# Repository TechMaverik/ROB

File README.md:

# ROB - Robotics On Board
<image src="static/studio.png" height=300px width=300px></image>

The project ROB is a robotic arm developed with in-house software, hardware assembly, and custom PCB design. ROB-Studio is the software used to interact with the robot.  
Version 1.0 features a 5-degree-of-freedom robotic arm powered by 6 servo motors, capable of lifting up to 50 g of payload. ROB-Studio is made using the software framework 
called HL-Engine 3, which acts as a middleware to communicate with Hardware and Software.

## ROB version 1.0
## Components Used
1. Servo Motor MG995
2. Servo Motor SG90
3. PCA9685 Servomotor Driver
4. OLED Display 128 x 64
5. ESP32

## Firmware
The baremetal interfacing and control system code is written in Micropython for ESP32

## Procedure of connection of motors and arm pieces
1. Upload the files under Firmware Folder
2. Make sure to provide a valid SSID and Password in the code as per your network connection.
3. Connect the servo motors from channel 0 to channel 5 in order base,shoulder,elbow,wrist-pitch,wrist-yaw,pick.
4. Make sure the servo is set to 90 degress.
5. Adjust the home position according to your requirements.

## Procedure to run the ROB-Studio
1. Install python 3.10 or later version
2. Create a virtual environment called .robot using the command <code>python3 -m venv .robot</code> ( One time )
3. Now run <code> pip3 install -r requirements.txt </code> ( One time )
4. Now run <code> chmod +x ./launcher </code> ( One time )
5. <b>To run the app run ./launcher.py </b>

## Alternative steps to run ROB-Studio
1. Follow the steps till line number 3
2. Now run <code>source .rob/bin/activate </code>
3. Now run <code>python run.py</code>

## ROB Studio
<image src="static/StudioHome.png"></image>
You can control the robor arm by adjusting the slider of each joints and by pressing the Move button. Inorder to record the particular orienttation, one has to adjust the arm and press the Record Button.
<image src="static/StudioRecord.png"></image>
Your recorded operations can be seen under Record and Play tab. You can start running the application by pressing the Play button.
<image src="static/StudioDevice.png"></image>
You can connect the ROB studion to the ROB by entering the IP Address displayed on ROB OLED Display. A sample is shown above.

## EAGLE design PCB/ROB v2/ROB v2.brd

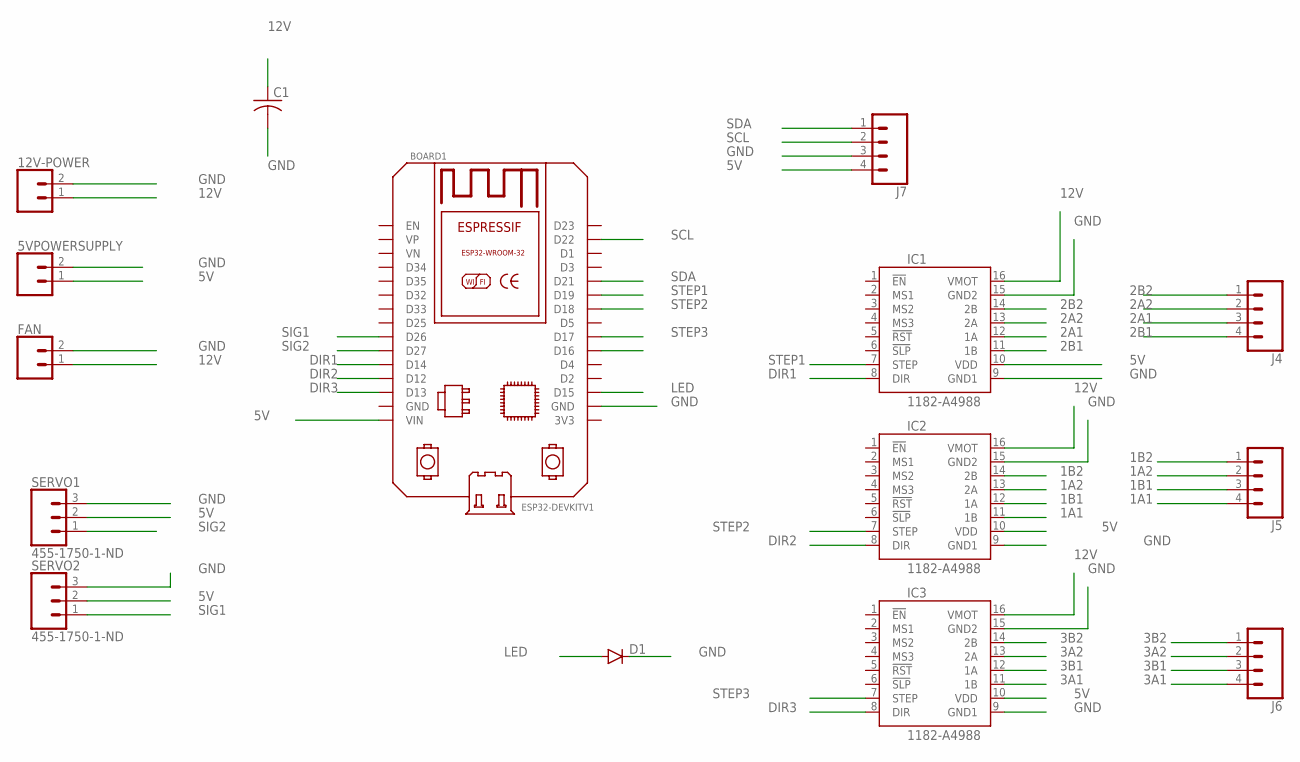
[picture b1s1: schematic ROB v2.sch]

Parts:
5VPOWERSUPPLY, 12V-POWER: CONN_02; 1X02
BOARD1: ESP32DEVKITV1; ESP32-DEVKITV1
C1: C-US050-075X075; C050-075X075
D1: DIODE; DIODE-1N4001-KIT
FAN: CONN_02; 1X02
IC1, IC2, IC3: 1182-A4988; A4988
J4, J5, J6: CONN_04LONGPADS; 1X04_LONGPADS
J7: CONN_04LOCK; 1X04_LOCK
SERVO1, SERVO2: 455-1750-1-ND; 1X03

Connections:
1A1: IC2.11 (1B), J5.4
1A2: IC2.13 (2A), J5.2
1B1: IC2.12 (1A), J5.3
1B2: IC2.14 (2B), J5.1
2A1: IC1.12 (1A), J4.3
2A2: IC1.13 (2A), J4.2
2B1: IC1.11 (1B), J4.4
2B2: IC1.14 (2B), J4.1
3A1: IC3.11 (1B), J6.4
3A2: IC3.13 (2A), J6.2
3B1: IC3.12 (1A), J6.3
3B2: IC3.14 (2B), J6.1
5V: 5VPOWERSUPPLY.1, BOARD1.VIN, IC1.10 (VDD), IC2.10 (VDD), IC3.10 (VDD), J7.4, SERVO1.2, SERVO2.2
12V: 12V-POWER.1, C1.1, FAN.1, IC1.16 (VMOT), IC2.16 (VMOT), IC3.16 (VMOT)
DIR1: BOARD1.D14, IC1.8 (DIR)
DIR2: BOARD1.D12, IC2.8 (DIR)
DIR3: BOARD1.D13, IC3.8 (DIR)
GND: 5VPOWERSUPPLY.2, 12V-POWER.2, BOARD1.GND@1 (GND), C1.2, D1.C, FAN.2, IC1.9 (GND1), IC1.15 (GND2), IC2.9 (GND1), IC2.15 (GND2), IC3.9 (GND1), IC3.15 (GND2), J7.3, SERVO1.3, SERVO2.3
LED: BOARD1.D15, D1.A
SCL: BOARD1.D22, J7.2
SDA: BOARD1.D21, J7.1
SIG1: BOARD1.D26, SERVO2.1
SIG2: BOARD1.D27, SERVO1.1
STEP1: BOARD1.D19, IC1.7 (STEP)
STEP2: BOARD1.D18, IC2.7 (STEP)
STEP3: BOARD1.D17, IC3.7 (STEP)

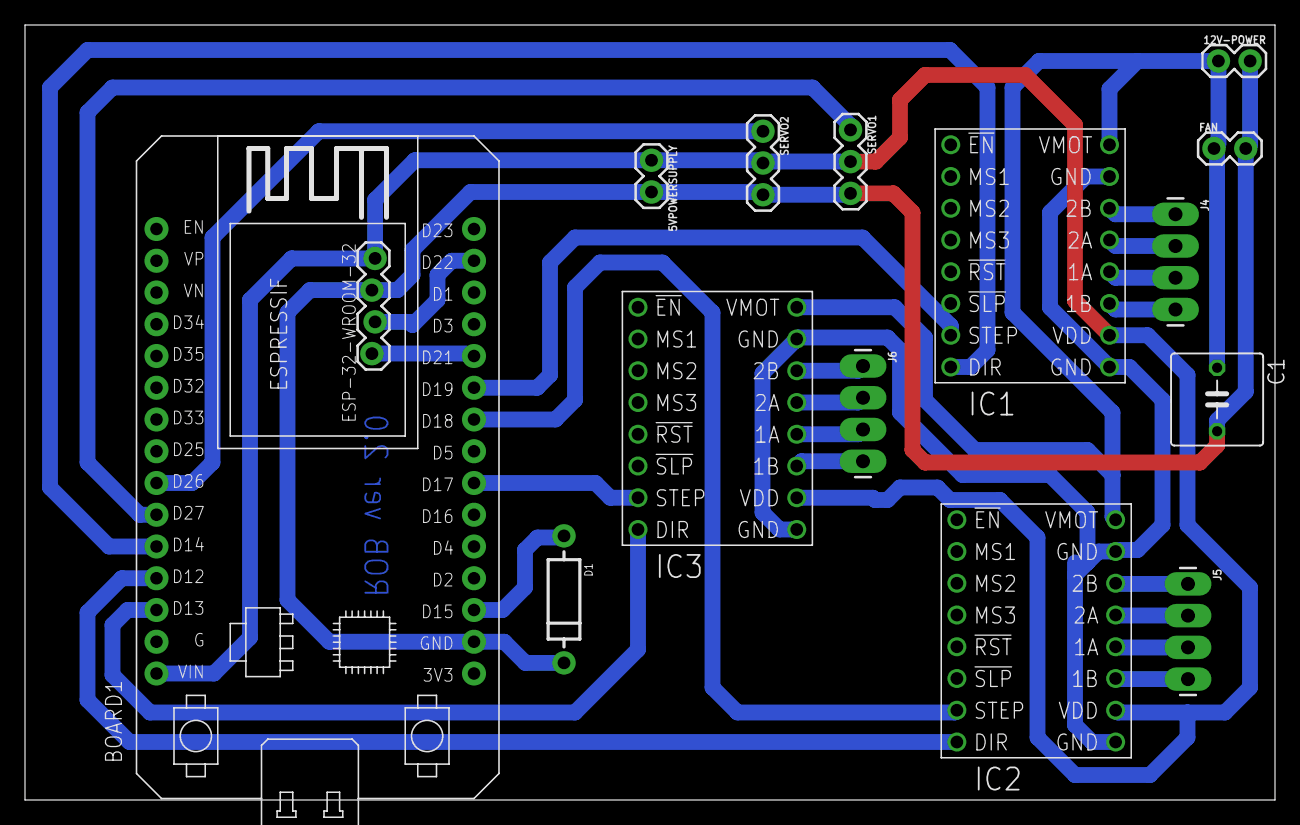
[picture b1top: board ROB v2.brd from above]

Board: 2 copper layers, 100.0 x 62.0 mm, 15 parts (0 on the bottom side), 26 nets.

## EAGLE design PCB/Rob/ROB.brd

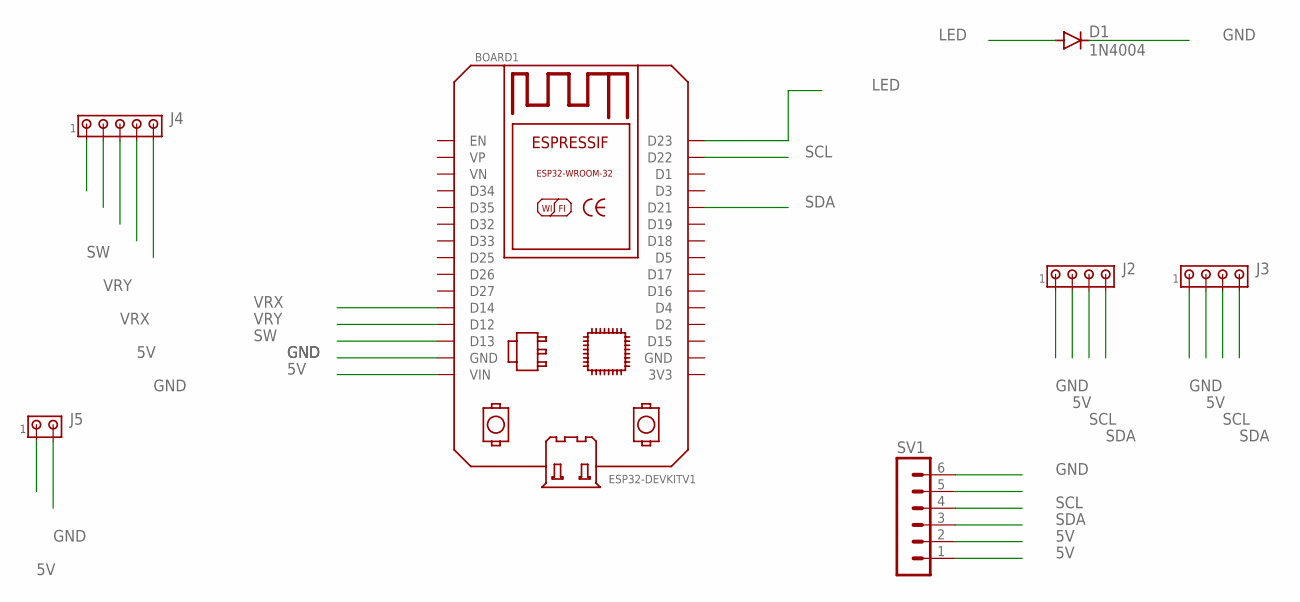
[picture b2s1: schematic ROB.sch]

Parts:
BOARD1: ESP32DEVKITV1; ESP32-DEVKITV1
D1: 1N4004; DO41-10
J2, J3: MTA04-100; 10X04MTA
J4: MTA05-100; 10X05MTA
J5: MTA02-156; 1X2MTA
SV1: MA06-1

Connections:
5V: BOARD1.VIN, J2.2, J3.2, J4.4, J5.1, SV1.1, SV1.2
GND: BOARD1.GND, D1.C, J2.1, J3.1, J4.5, J5.2, SV1.6
LED: BOARD1.D23, D1.A
SCL: BOARD1.D22, J2.3, J3.3, SV1.4
SDA: BOARD1.D21, J2.4, J3.4, SV1.3
SW: BOARD1.D13, J4.1
VRX: BOARD1.D14, J4.3
VRY: BOARD1.D12, J4.2

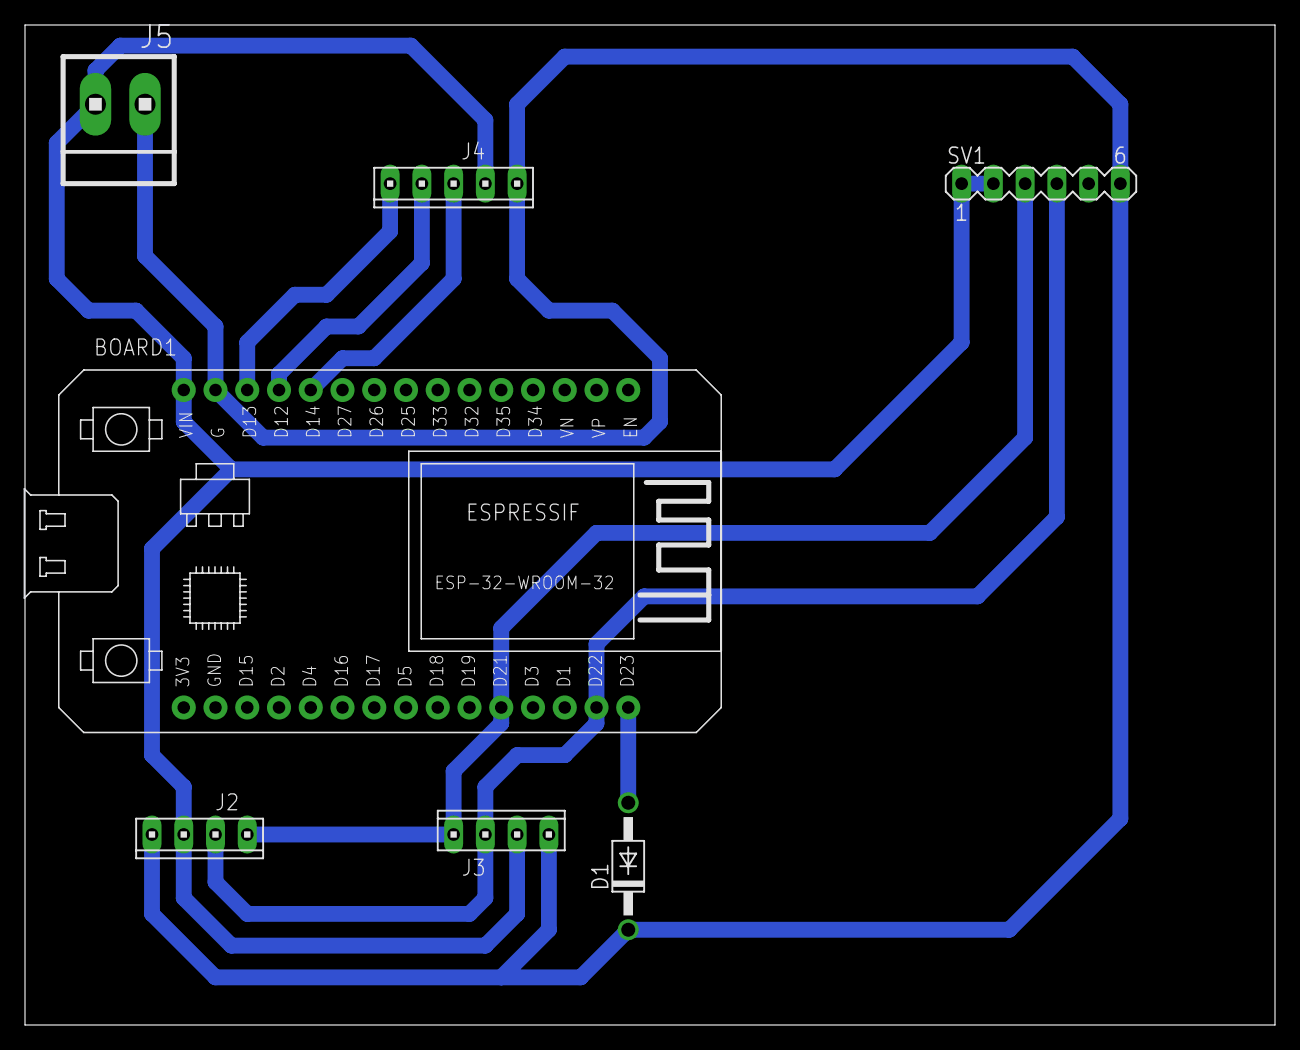
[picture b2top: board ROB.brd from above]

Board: 2 copper layers, 100.0 x 80.0 mm, 7 parts (0 on the bottom side), 8 nets.

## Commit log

2025-08-27 PCB Designing
2025-08-28 Firmware updates Platform IO
2025-08-28 updated channel
2025-08-28 oled display added
2025-08-30 rob removed display update
2025-09-04 removed firmware in cpp
2025-09-08 pcb files
2025-09-09 initial micro python firmware commit
2025-09-09 new configuration and new control system
2025-09-09 updated firmware
2025-09-09 updated base prepositions and amotion planner
2025-09-09 Architectural Diagrram
2025-09-10 fine tuning firmware
2025-09-10 fine tuning
2025-09-11 updated router
2025-09-11 updated main
2025-09-11 updated html home page
2025-09-12 new ui
2025-09-12 ui fix primary
2025-09-14 Updated the UI design and base mapper functionality update
2025-09-15 removed launcher from firmware
2025-09-15 Firmware update
2025-09-15 Firmware update on display
2025-09-15 updated the feed back system to the front end
2025-09-15 added new submit button
2025-09-15 new port added and git ignore updated
2025-09-16 updated home position
2025-09-16 update other functionalities
2025-09-16 updated the position
2025-09-17 rob record and play in built
2025-09-17 removed home position button
2025-09-19 setup updates
2025-09-19 Create README.md
    Added Read me file
2025-09-19 updated read me
2025-09-19 renamed
2025-09-21 version 2 pcb design updates
2025-09-23 exception handling
2025-09-24 Added about and documentation in code
2025-09-24 About
2025-09-24 updated about
2025-09-24 added additional exception handling
2025-09-24 updated schematics and board
2025-09-24 removed cache
2025-09-24 new firmware with motion planner
2025-09-25 Motion Planner updated

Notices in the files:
parts and their libraries:
SparkFun-Connectors: Licensing: Creative Commons ShareAlike 4.0 International - https://creativecommons.org/licenses/by-sa/4.0
